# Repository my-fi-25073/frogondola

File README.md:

# gondola
gondola layout keyboard pcb &amp; firmware &amp; plate.

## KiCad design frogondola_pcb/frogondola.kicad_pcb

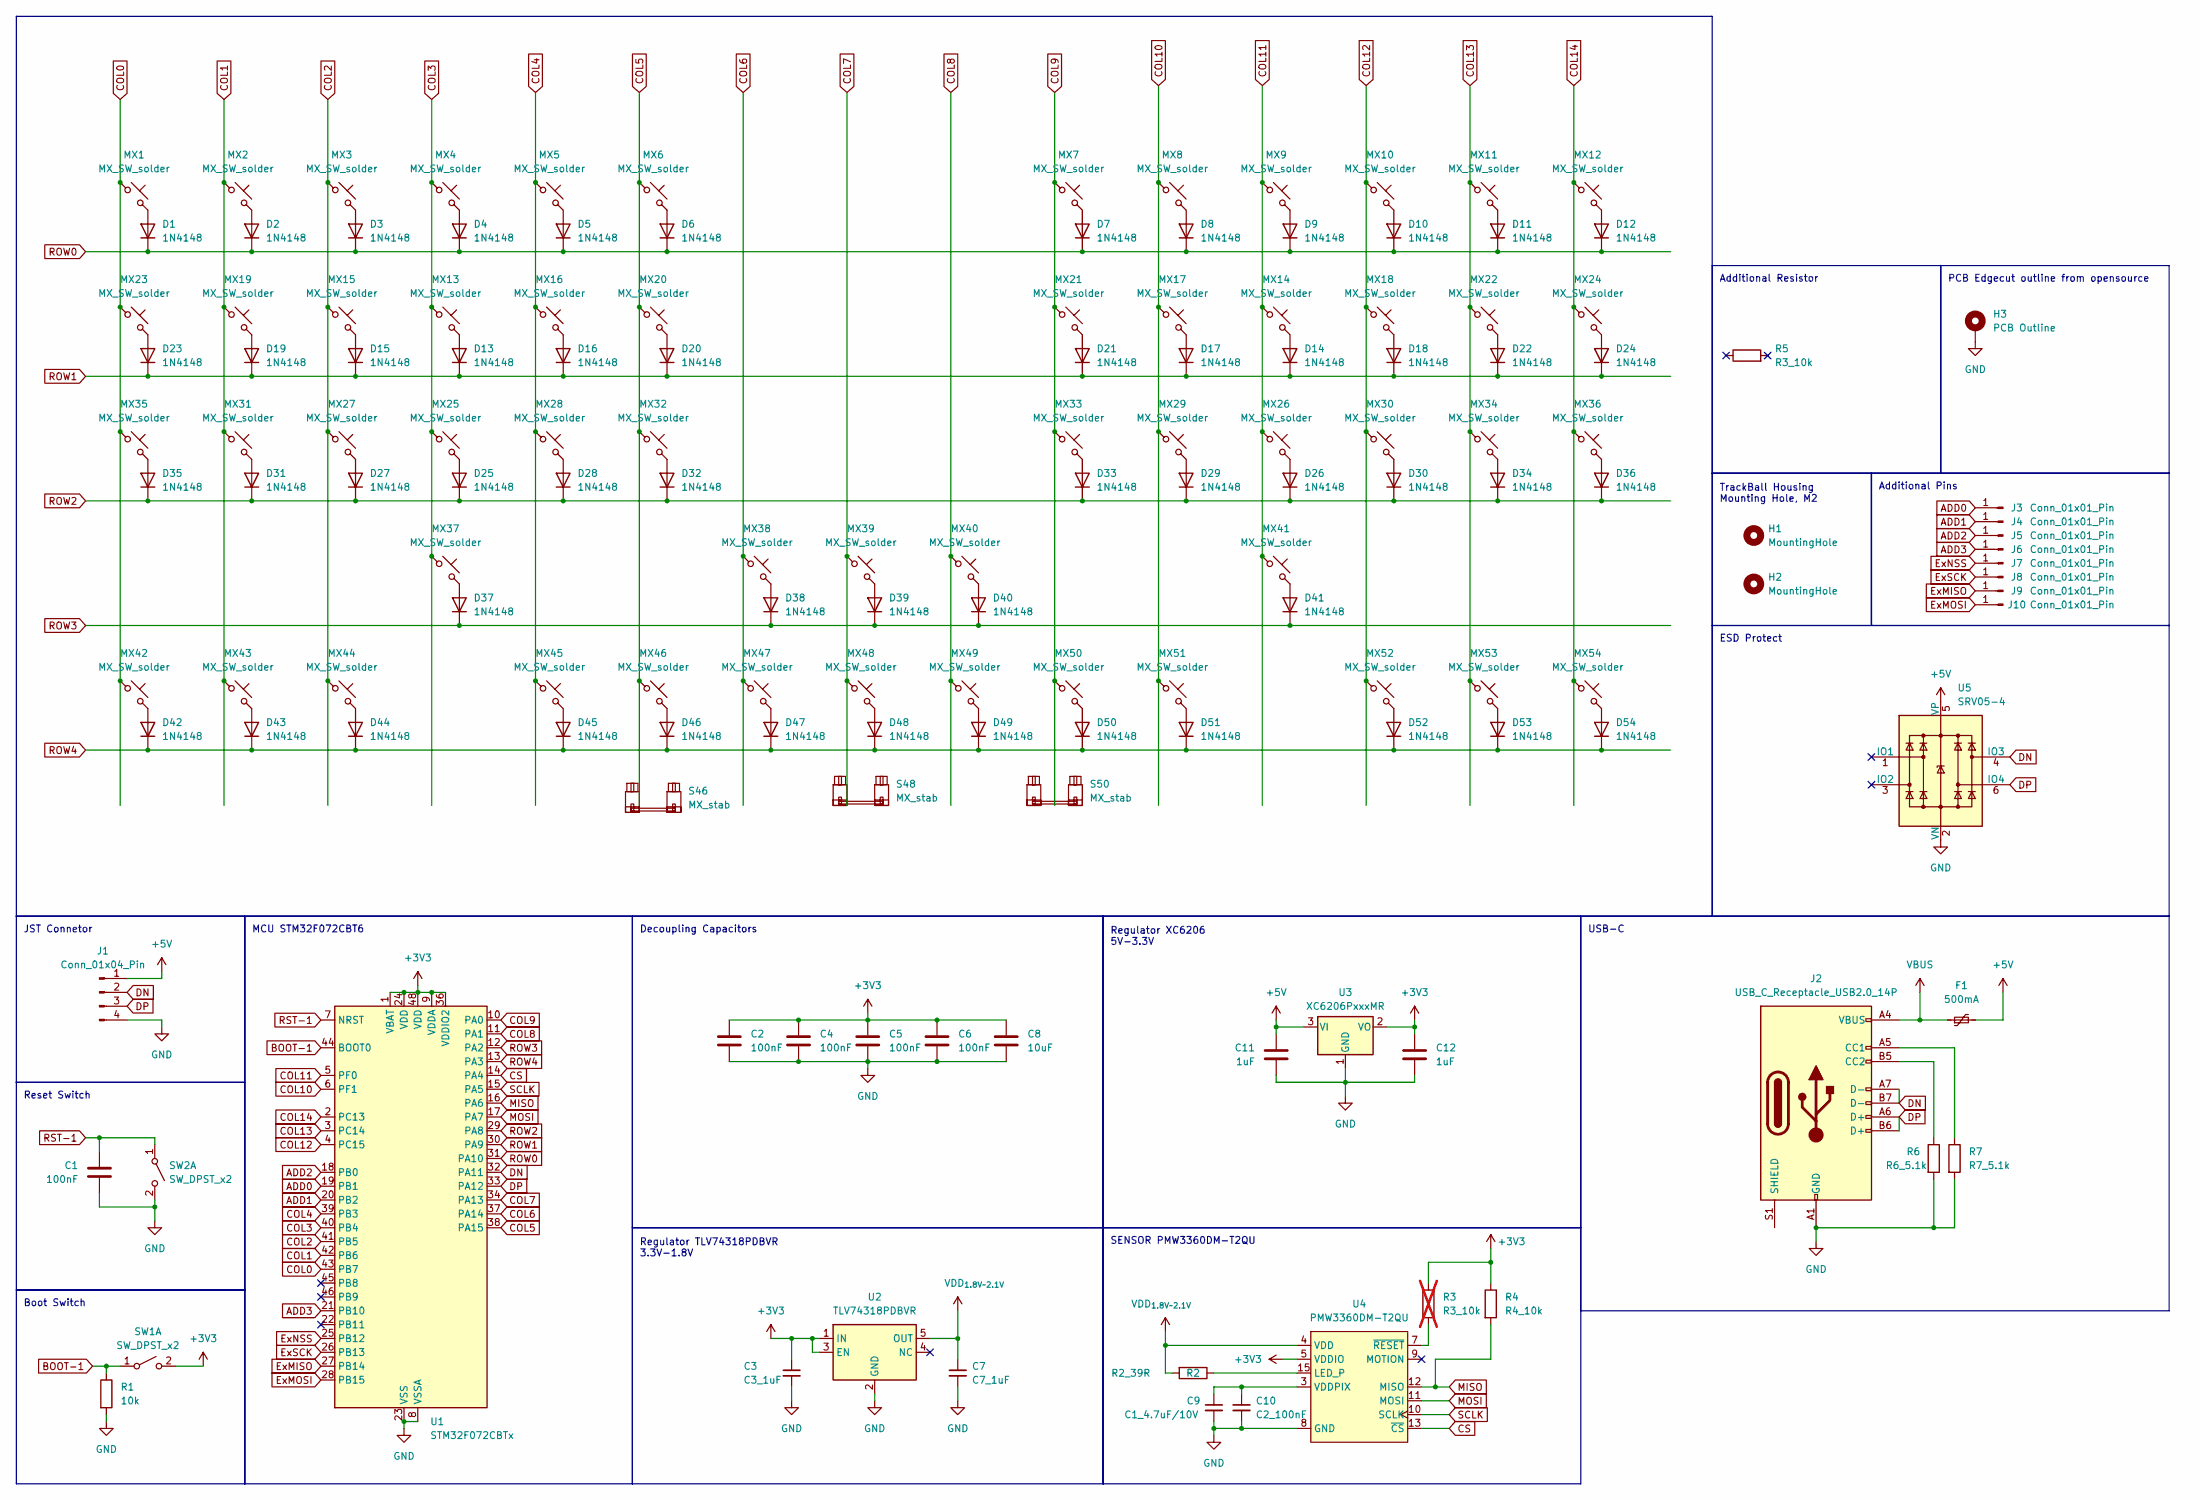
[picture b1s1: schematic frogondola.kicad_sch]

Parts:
C1, C2, C4, C5, C6: 100nF; C_0402_1005Metric
C3: C3_1uF; C_0402_1005Metric
C7: C7_1uF; C_0402_1005Metric
C8: 10uF; C_0402_1005Metric
C9: C1_4.7uF/10V; C_0402_1005Metric
C10: C2_100nF; C_0402_1005Metric
C11, C12: 1uF; C_0402_1005Metric
D1, D2, D3, D4, D5, D6, D7, D8, D9, D10, D11, D12, D13, D14, D15, D16, D17, D18, D19, D20, D21, D22, D23, D24, D25, D26, D27, D28, D29, D30, D31, D32, D33, D34, D35, D36, D37, D38, D39, D40, D41, D42, D43, D44, D45, D46, D47, D48, D49, D50, D51, D52, D53, D54: 1N4148; D_SOD-123
F1: 500mA; Fuse_1206_3216Metric; LCSC C70076
H1: MountingHole; MountingHole_2.2mm_M2_ISO14580_Pad
H2: MountingHole; MountingHole_2.2mm_M2_ISO7380_Pad
H3: PCB Outline; L60 Outline
J1: Conn_01x04_Pin; JST_SH_SM04B-SRSS-TB_1x04-1MP_P1.00mm_Horizontal
J2: USB_C_Receptacle_USB2.0_14P; USB_C_Receptacle_HRO_TYPE-C-31-M-12; MPN C2894897
J3, J4, J5, J6: Conn_01x01_Pin; TestPoint_Pad_1.5x1.5mm
J7, J8, J9, J10: Conn_01x01_Pin; TestPoint_THTPad_1.5x1.5mm_Drill0.7mm
MX1, MX2, MX3, MX4, MX5, MX6, MX7, MX8, MX9, MX10, MX11, MX12, MX13, MX14, MX15, MX16, MX17, MX18, MX19, MX20, MX21, MX22, MX23, MX24, MX25, MX26, MX27, MX28, MX29, MX30, MX31, MX32, MX33, MX34, MX35, MX36, MX37, MX38, MX39, MX40, MX41, MX42, MX43, MX44, MX45, MX46, MX47, MX48, MX49, MX50, MX51, MX52, MX53, MX54: MX_SW_solder; SW_MX_1u
R1: 10k; R_0402_1005Metric
R2: R2_39R; R_0402_1005Metric
R3: R3_10k; R_0805_2012Metric_Pad1.20x1.40mm_HandSolder; not fitted
R4: R4_10k; R_0402_1005Metric
R5: R3_10k; R_0805_2012Metric_Pad1.20x1.40mm_HandSolder
R6: R6_5.1k; R_0402_1005Metric
R7: R7_5.1k; R_0402_1005Metric
S46, S50: MX_stab; STAB_MX_P_3u
S48: MX_stab; STAB_MX_P_7u
SW1, SW2: SW_DPST_x2; SW_Push_1P1T_XKB_TS-1187A; MPN C318884
U1: STM32F072CBTx; LQFP-48_7x7mm_P0.5mm; MPN C81720
U2: TLV74318PDBVR; SOT-23-5; MPN C485152
U3: XC6206PxxxMR; SOT-23-3; MPN C5148692
U4: PMW3360DM-T2QU; PMW3360DM-T2QU 16Pin
U5: SRV05-4; SOT-23-6; MPN C7420376

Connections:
+3V3: C2.1, C3.1, C4.1, C5.1, C6.1, C8.1, C12.1, R3.1, R4.1, SW1.2 (B), U1.1 (VBAT), U1.9 (VDDA), U1.24 (VDD), U1.36 (VDDIO2), U1.48 (VDD), U2.1 (IN), U2.3 (EN), U3.2 (VO), U4.5 (VDDIO)
+5V: C11.1, F1.2, J1.1, U3.3 (VI), U5.5 (VP)
ADD0: J3.1, U1.19 (PB1)
ADD1: J4.1, U1.20 (PB2)
ADD2: J5.1, U1.18 (PB0)
ADD3: J6.1, U1.21 (PB10)
BOOT-1: R1.1, SW1.1 (A), U1.44 (BOOT0)
COL0: MX1.1, MX23.1, MX35.1, MX42.1, U1.43 (PB7)
COL1: MX2.1, MX19.1, MX31.1, MX43.1, U1.42 (PB6)
COL2: MX3.1, MX15.1, MX27.1, MX44.1, U1.41 (PB5)
COL3: MX4.1, MX13.1, MX25.1, MX37.1, U1.40 (PB4)
COL4: MX5.1, MX16.1, MX28.1, MX45.1, U1.39 (PB3)
COL5: MX6.1, MX20.1, MX32.1, MX46.1, U1.38 (PA15)
COL6: MX38.1, MX47.1, U1.37 (PA14)
COL7: MX39.1, MX48.1, U1.34 (PA13)
COL8: MX40.1, MX49.1, U1.11 (PA1)
COL9: MX7.1, MX21.1, MX33.1, MX50.1, U1.10 (PA0)
COL10: MX8.1, MX17.1, MX29.1, MX51.1, U1.6 (PF1)
COL11: MX9.1, MX14.1, MX26.1, MX41.1, U1.5 (PF0)
COL12: MX10.1, MX18.1, MX30.1, MX52.1, U1.4 (PC15)
COL13: MX11.1, MX22.1, MX34.1, MX53.1, U1.3 (PC14)
COL14: MX12.1, MX24.1, MX36.1, MX54.1, U1.2 (PC13)
CS: U1.14 (PA4), U4.13 (~CS)
DN: J1.2, J2.A7 (D-), J2.B7 (D-), U1.32 (PA11), U5.4 (IO3)
DP: J1.3, J2.A6 (D+), J2.B6 (D+), U1.33 (PA12), U5.6 (IO4)
ExMISO: J9.1, U1.27 (PB14)
ExMOSI: J10.1, U1.28 (PB15)
ExNSS: J7.1, U1.25 (PB12)
ExSCK: J8.1, U1.26 (PB13)
GND: C1.2, C2.2, C3.2, C4.2, C5.2, C6.2, C7.2, C8.2, C9.2, C10.2, C11.2, C12.2, H3.1, J1.4, J2.A1 (GND), J2.A12 (GND), J2.B1 (GND), J2.B12 (GND), R1.2, R6.2, R7.2, SW2.2 (B), U1.8 (VSSA), U1.23 (VSS), U1.35 (VSS), U1.47 (VSS), U2.2 (GND), U3.1 (GND), U4.8 (GND), U5.2 (VN)
MISO: R4.2, U1.16 (PA6), U4.12 (MISO)
MOSI: U1.17 (PA7), U4.11 (MOSI)
unnamed: D1.2 (A), MX1.2
unnamed: D2.2 (A), MX2.2
unnamed: D3.2 (A), MX3.2
unnamed: D4.2 (A), MX4.2
unnamed: D5.2 (A), MX5.2
unnamed: D6.2 (A), MX6.2
unnamed: D7.2 (A), MX7.2
unnamed: D8.2 (A), MX8.2
unnamed: D9.2 (A), MX9.2
unnamed: D10.2 (A), MX10.2
unnamed: D11.2 (A), MX11.2
unnamed: D12.2 (A), MX12.2
unnamed: D13.2 (A), MX13.2
unnamed: D14.2 (A), MX14.2
unnamed: D15.2 (A), MX15.2
unnamed: D16.2 (A), MX16.2
unnamed: D17.2 (A), MX17.2
unnamed: D18.2 (A), MX18.2
unnamed: D19.2 (A), MX19.2
unnamed: D20.2 (A), MX20.2
unnamed: D21.2 (A), MX21.2
unnamed: D22.2 (A), MX22.2
unnamed: D23.2 (A), MX23.2
unnamed: D24.2 (A), MX24.2
unnamed: D25.2 (A), MX25.2
unnamed: D26.2 (A), MX26.2
unnamed: D27.2 (A), MX27.2
unnamed: D28.2 (A), MX28.2
unnamed: D29.2 (A), MX29.2
unnamed: D30.2 (A), MX30.2
unnamed: D31.2 (A), MX31.2
unnamed: D32.2 (A), MX32.2
unnamed: D33.2 (A), MX33.2
unnamed: D34.2 (A), MX34.2
unnamed: D35.2 (A), MX35.2
unnamed: D36.2 (A), MX36.2
unnamed: D37.2 (A), MX37.2
unnamed: D38.2 (A), MX38.2
unnamed: D39.2 (A), MX39.2
unnamed: D40.2 (A), MX40.2
unnamed: D41.2 (A), MX41.2
unnamed: D42.2 (A), MX42.2
unnamed: D43.2 (A), MX43.2
unnamed: D44.2 (A), MX44.2
unnamed: D45.2 (A), MX45.2
unnamed: D46.2 (A), MX46.2
unnamed: D47.2 (A), MX47.2
unnamed: D48.2 (A), MX48.2
unnamed: D49.2 (A), MX49.2
unnamed: D50.2 (A), MX50.2
unnamed: D51.2 (A), MX51.2
unnamed: D52.2 (A), MX52.2
unnamed: D53.2 (A), MX53.2
unnamed: D54.2 (A), MX54.2
unnamed: J2.A5 (CC1), R7.1
unnamed: J2.B5 (CC2), R6.1
unnamed: R2.1, U4.15 (LED_P)
unnamed: C9.1, C10.1, U4.3 (VDDPIX)
unnamed: R3.2, U4.7 (~RESET)
ROW0: D1.1 (K), D2.1 (K), D3.1 (K), D4.1 (K), D5.1 (K), D6.1 (K), D7.1 (K), D8.1 (K), D9.1 (K), D10.1 (K), D11.1 (K), D12.1 (K), U1.31 (PA10)
ROW1: D13.1 (K), D14.1 (K), D15.1 (K), D16.1 (K), D17.1 (K), D18.1 (K), D19.1 (K), D20.1 (K), D21.1 (K), D22.1 (K), D23.1 (K), D24.1 (K), U1.30 (PA9)
ROW2: D25.1 (K), D26.1 (K), D27.1 (K), D28.1 (K), D29.1 (K), D30.1 (K), D31.1 (K), D32.1 (K), D33.1 (K), D34.1 (K), D35.1 (K), D36.1 (K), U1.29 (PA8)
ROW3: D37.1 (K), D38.1 (K), D39.1 (K), D40.1 (K), D41.1 (K), U1.12 (PA2)
ROW4: D42.1 (K), D43.1 (K), D44.1 (K), D45.1 (K), D46.1 (K), D47.1 (K), D48.1 (K), D49.1 (K), D50.1 (K), D51.1 (K), D52.1 (K), D53.1 (K), D54.1 (K), U1.13 (PA3)
RST-1: C1.1, SW2.1 (A), U1.7 (NRST)
SCLK: U1.15 (PA5), U4.10 (SCLK)
VBUS: F1.1, J2.A4 (VBUS), J2.A9 (VBUS), J2.B4 (VBUS), J2.B9 (VBUS)
VDD_{1.8V~2.1V}: C7.1, R2.2, U2.5 (OUT), U4.4 (VDD)

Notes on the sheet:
TrackBall Housing Mounting Hole, M2
Additional Resistor
ESD Protect
Regulator TLV74318PDBVR 3.3V-1.8V
Decoupling Capacitors
Regulator XC6206 5V-3.3V
MCU STM32F072CBT6
USB-C
Additional Pins
Reset Switch
Boot Switch
SENSOR PMW3360DM-T2QU
JST Connetor
PCB Edgecut outline from opensource

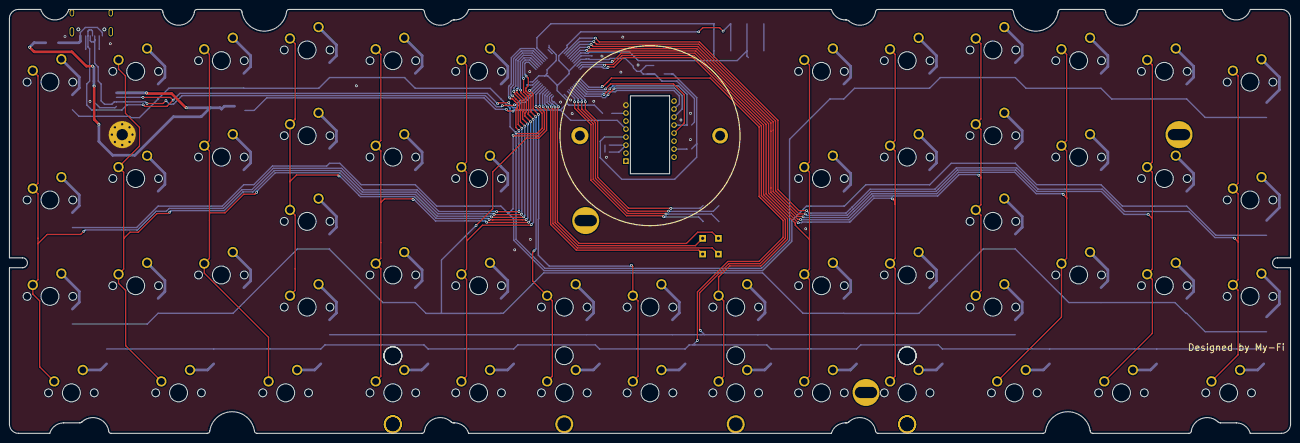
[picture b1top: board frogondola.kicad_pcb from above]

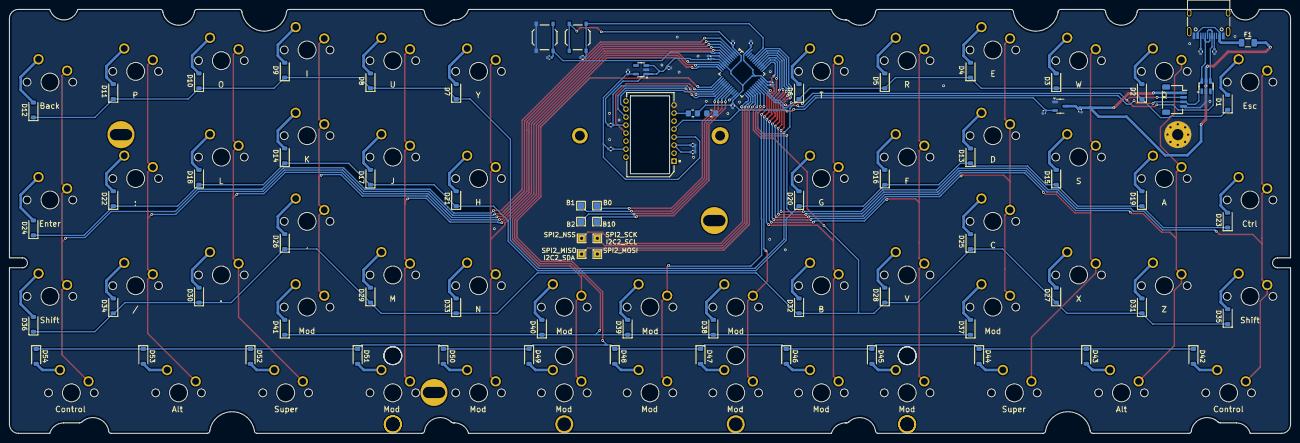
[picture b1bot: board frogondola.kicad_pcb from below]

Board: 2 copper layers, 284.7 x 94.2 mm, 151 parts (91 on the bottom side), 100 nets.

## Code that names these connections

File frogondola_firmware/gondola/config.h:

#pragma once

// https://docs.qmk.fm/drivers/spi
// SPI Pins for PMW3360 - STM32F072

// https://www.st.com/resource/en/datasheet/stm32f072cb.pdf
// 38 page

//  PA4 - GPIO (CS)
//  PA6 - SPI1_MISO
//  PA7 - SPI1_MOSI
//  PA5 - SPI1_SCK

#define SPI_SCK_PAL_MODE 0
#define SPI_MISO_PAL_MODE 0
#define SPI_MOSI_PAL_MODE 0

#define PMW33XX_CS_PIN A4 // SPI CS pin.
#define SPI_SCK_PIN A5
#define SPI_MISO_PIN A6
#define SPI_MOSI_PIN A7

#define POINTING_DEVICE_INVERT_Y

#define DYNAMIC_KEYMAP_LAYER_COUNT 6

/* Optional. */
#define PMW33XX_CPI 800             // The CPI range is 100-12000, in increments of 100. Defaults to 1600 CPI.
#define PMW33XX_CLOCK_SPEED 2000000 // Sets the clock speed that the sensor runs at. Defaults to 2000000
#define MOUSE_EXTENDED_REPORT       // Use -32767 to 32767, instead of just -127 to 127.
#define WHEEL_EXTENDED_REPORT       // Use -32767 to 32767, instead of just -127 to 127.

#define USB_POLLING_INTERVAL_MS 2

#define PMW33XX_SPI_DIVISOR 64
#define POINTING_DEVICE_TASK_THROTTLE_MS 2
#define FORCE_NKRO

// https://docs.qmk.fm/features/pointing_device

// Addintion GPIO Pins for keyboard

// ADD0 - F1
// ADD1 - F0
// ADD2 - A0
// ADD3 - C15
// ADD4 - A1
// ADD5 - C14
// ADD6 - A2
// ADD7 - C13

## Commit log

2025-04-15 Added schematic and PCB matrix layout
2025-04-16 Adde L60 outline footprint from https://github.com/dededecline/SST60, will update license too.
2025-04-18 updated pcb matrix & route.
2025-04-22 Routed usb, jst, pmw3360, column matrix.
2025-04-26 Almost done!
2025-05-08 added sample plate file
2025-06-08 Added qmk firmware and new plate file
2026-01-19 Added 3d models
